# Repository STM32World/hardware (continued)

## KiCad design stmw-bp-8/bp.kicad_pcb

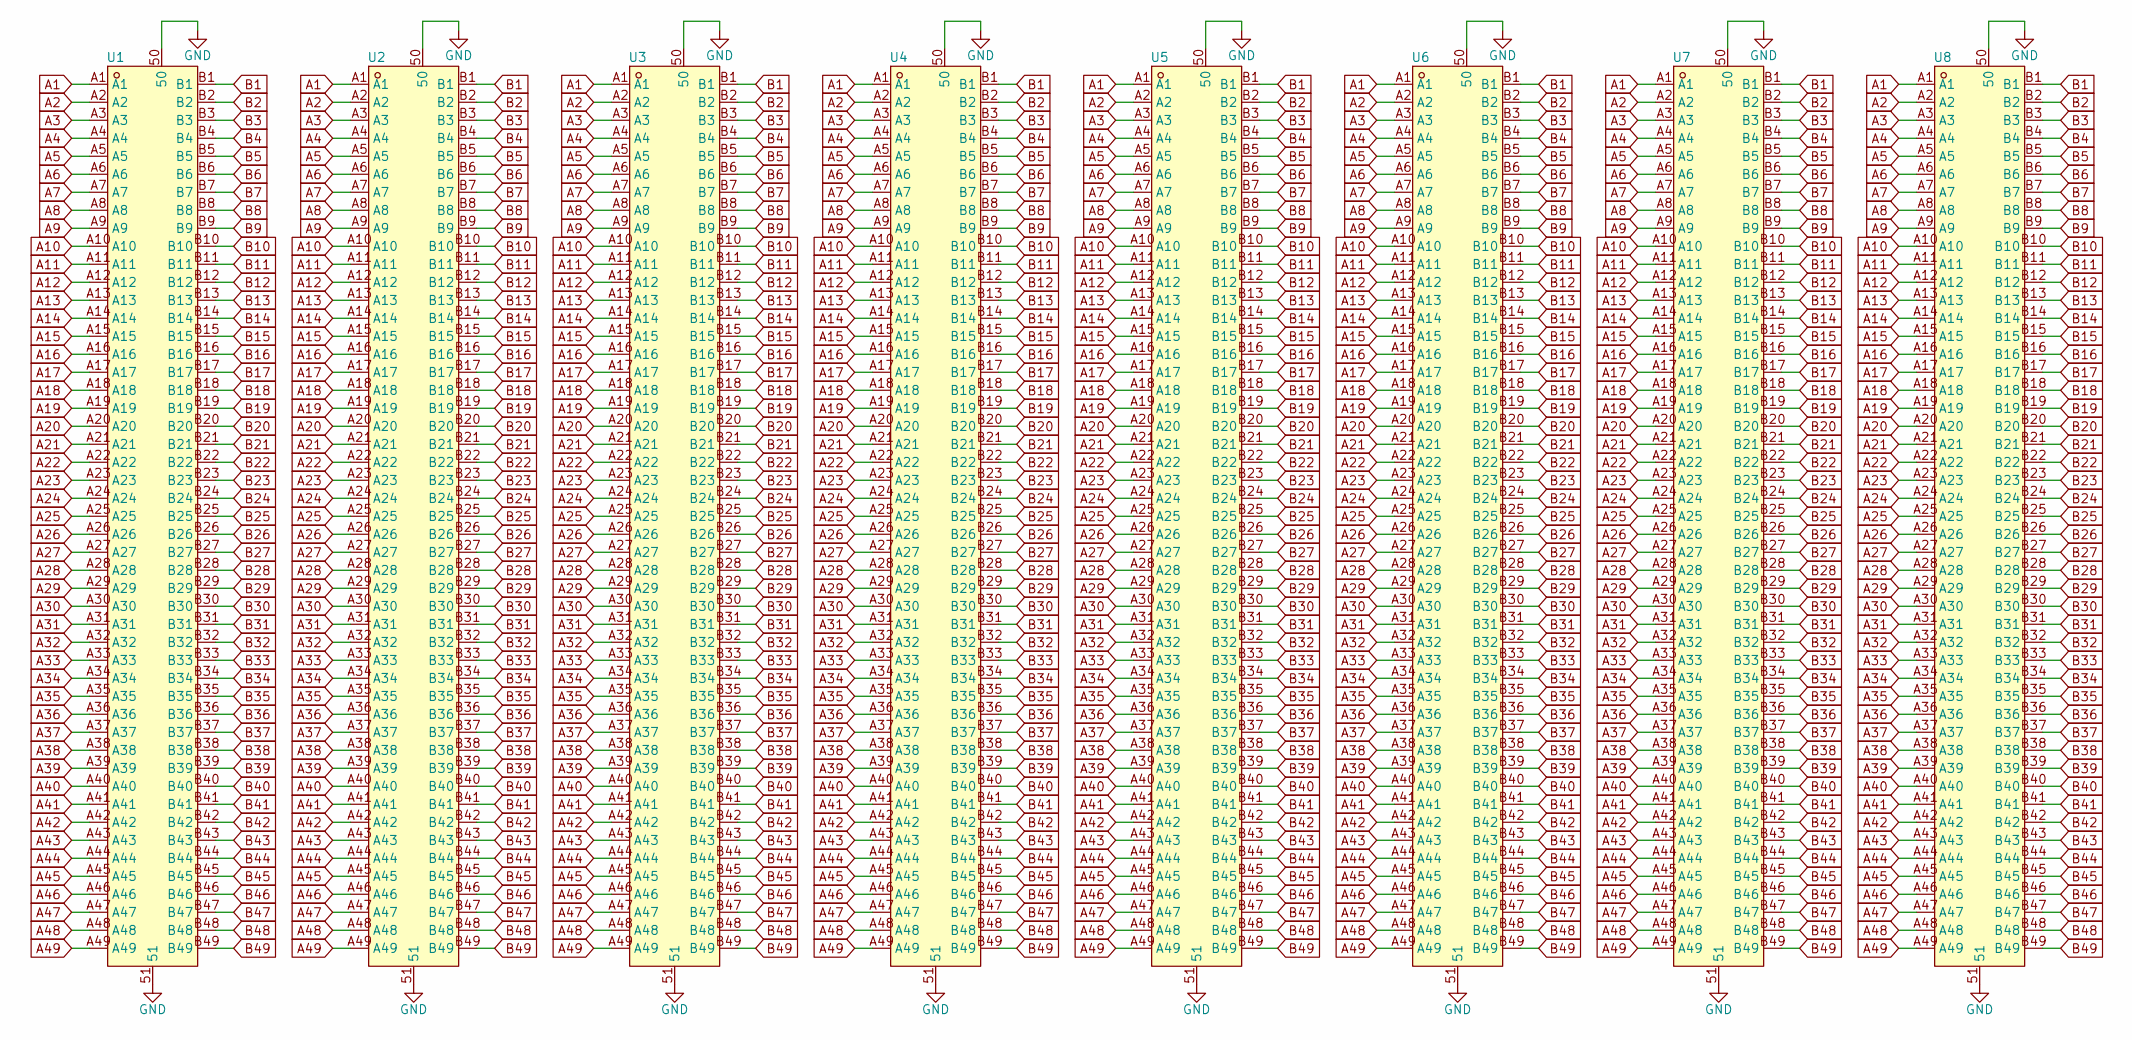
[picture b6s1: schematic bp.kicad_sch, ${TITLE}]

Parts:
U1, U2, U3, U4, U5, U6, U7, U8: X1611WVS-98-9TV01; CONN-SMD_98P-P1.00-V_3133; LCSC C21263085

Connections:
A1: U1.A1, U2.A1, U3.A1, U4.A1, U5.A1, U6.A1, U7.A1, U8.A1
A2: U1.A2, U2.A2, U3.A2, U4.A2, U5.A2, U6.A2, U7.A2, U8.A2
A3: U1.A3, U2.A3, U3.A3, U4.A3, U5.A3, U6.A3, U7.A3, U8.A3
A4: U1.A4, U2.A4, U3.A4, U4.A4, U5.A4, U6.A4, U7.A4, U8.A4
A5: U1.A5, U2.A5, U3.A5, U4.A5, U5.A5, U6.A5, U7.A5, U8.A5
A6: U1.A6, U2.A6, U3.A6, U4.A6, U5.A6, U6.A6, U7.A6, U8.A6
A7: U1.A7, U2.A7, U3.A7, U4.A7, U5.A7, U6.A7, U7.A7, U8.A7
A8: U1.A8, U2.A8, U3.A8, U4.A8, U5.A8, U6.A8, U7.A8, U8.A8
A9: U1.A9, U2.A9, U3.A9, U4.A9, U5.A9, U6.A9, U7.A9, U8.A9
A10: U1.A10, U2.A10, U3.A10, U4.A10, U5.A10, U6.A10, U7.A10, U8.A10
A11: U1.A11, U2.A11, U3.A11, U4.A11, U5.A11, U6.A11, U7.A11, U8.A11
A12: U1.A12, U2.A12, U3.A12, U4.A12, U5.A12, U6.A12, U7.A12, U8.A12
A13: U1.A13, U2.A13, U3.A13, U4.A13, U5.A13, U6.A13, U7.A13, U8.A13
A14: U1.A14, U2.A14, U3.A14, U4.A14, U5.A14, U6.A14, U7.A14, U8.A14
A15: U1.A15, U2.A15, U3.A15, U4.A15, U5.A15, U6.A15, U7.A15, U8.A15
A16: U1.A16, U2.A16, U3.A16, U4.A16, U5.A16, U6.A16, U7.A16, U8.A16
A17: U1.A17, U2.A17, U3.A17, U4.A17, U5.A17, U6.A17, U7.A17, U8.A17
A18: U1.A18, U2.A18, U3.A18, U4.A18, U5.A18, U6.A18, U7.A18, U8.A18
A19: U1.A19, U2.A19, U3.A19, U4.A19, U5.A19, U6.A19, U7.A19, U8.A19
A20: U1.A20, U2.A20, U3.A20, U4.A20, U5.A20, U6.A20, U7.A20, U8.A20
A21: U1.A21, U2.A21, U3.A21, U4.A21, U5.A21, U6.A21, U7.A21, U8.A21
A22: U1.A22, U2.A22, U3.A22, U4.A22, U5.A22, U6.A22, U7.A22, U8.A22
A23: U1.A23, U2.A23, U3.A23, U4.A23, U5.A23, U6.A23, U7.A23, U8.A23
A24: U1.A24, U2.A24, U3.A24, U4.A24, U5.A24, U6.A24, U7.A24, U8.A24
A25: U1.A25, U2.A25, U3.A25, U4.A25, U5.A25, U6.A25, U7.A25, U8.A25
A26: U1.A26, U2.A26, U3.A26, U4.A26, U5.A26, U6.A26, U7.A26, U8.A26
A27: U1.A27, U2.A27, U3.A27, U4.A27, U5.A27, U6.A27, U7.A27, U8.A27
A28: U1.A28, U2.A28, U3.A28, U4.A28, U5.A28, U6.A28, U7.A28, U8.A28
A29: U1.A29, U2.A29, U3.A29, U4.A29, U5.A29, U6.A29, U7.A29, U8.A29
A30: U1.A30, U2.A30, U3.A30, U4.A30, U5.A30, U6.A30, U7.A30, U8.A30
A31: U1.A31, U2.A31, U3.A31, U4.A31, U5.A31, U6.A31, U7.A31, U8.A31
A32: U1.A32, U2.A32, U3.A32, U4.A32, U5.A32, U6.A32, U7.A32, U8.A32
A33: U1.A33, U2.A33, U3.A33, U4.A33, U5.A33, U6.A33, U7.A33, U8.A33
A34: U1.A34, U2.A34, U3.A34, U4.A34, U5.A34, U6.A34, U7.A34, U8.A34
A35: U1.A35, U2.A35, U3.A35, U4.A35, U5.A35, U6.A35, U7.A35, U8.A35
A36: U1.A36, U2.A36, U3.A36, U4.A36, U5.A36, U6.A36, U7.A36, U8.A36
A37: U1.A37, U2.A37, U3.A37, U4.A37, U5.A37, U6.A37, U7.A37, U8.A37
A38: U1.A38, U2.A38, U3.A38, U4.A38, U5.A38, U6.A38, U7.A38, U8.A38
A39: U1.A39, U2.A39, U3.A39, U4.A39, U5.A39, U6.A39, U7.A39, U8.A39
A40: U1.A40, U2.A40, U3.A40, U4.A40, U5.A40, U6.A40, U7.A40, U8.A40
A41: U1.A41, U2.A41, U3.A41, U4.A41, U5.A41, U6.A41, U7.A41, U8.A41
A42: U1.A42, U2.A42, U3.A42, U4.A42, U5.A42, U6.A42, U7.A42, U8.A42
A43: U1.A43, U2.A43, U3.A43, U4.A43, U5.A43, U6.A43, U7.A43, U8.A43
A44: U1.A44, U2.A44, U3.A44, U4.A44, U5.A44, U6.A44, U7.A44, U8.A44
A45: U1.A45, U2.A45, U3.A45, U4.A45, U5.A45, U6.A45, U7.A45, U8.A45
A46: U1.A46, U2.A46, U3.A46, U4.A46, U5.A46, U6.A46, U7.A46, U8.A46
A47: U1.A47, U2.A47, U3.A47, U4.A47, U5.A47, U6.A47, U7.A47, U8.A47
A48: U1.A48, U2.A48, U3.A48, U4.A48, U5.A48, U6.A48, U7.A48, U8.A48
A49: U1.A49, U2.A49, U3.A49, U4.A49, U5.A49, U6.A49, U7.A49, U8.A49
B1: U1.B1, U2.B1, U3.B1, U4.B1, U5.B1, U6.B1, U7.B1, U8.B1
B2: U1.B2, U2.B2, U3.B2, U4.B2, U5.B2, U6.B2, U7.B2, U8.B2
B3: U1.B3, U2.B3, U3.B3, U4.B3, U5.B3, U6.B3, U7.B3, U8.B3
B4: U1.B4, U2.B4, U3.B4, U4.B4, U5.B4, U6.B4, U7.B4, U8.B4
B5: U1.B5, U2.B5, U3.B5, U4.B5, U5.B5, U6.B5, U7.B5, U8.B5
B6: U1.B6, U2.B6, U3.B6, U4.B6, U5.B6, U6.B6, U7.B6, U8.B6
B7: U1.B7, U2.B7, U3.B7, U4.B7, U5.B7, U6.B7, U7.B7, U8.B7
B8: U1.B8, U2.B8, U3.B8, U4.B8, U5.B8, U6.B8, U7.B8, U8.B8
B9: U1.B9, U2.B9, U3.B9, U4.B9, U5.B9, U6.B9, U7.B9, U8.B9
B10: U1.B10, U2.B10, U3.B10, U4.B10, U5.B10, U6.B10, U7.B10, U8.B10
B11: U1.B11, U2.B11, U3.B11, U4.B11, U5.B11, U6.B11, U7.B11, U8.B11
B12: U1.B12, U2.B12, U3.B12, U4.B12, U5.B12, U6.B12, U7.B12, U8.B12
B13: U1.B13, U2.B13, U3.B13, U4.B13, U5.B13, U6.B13, U7.B13, U8.B13
B14: U1.B14, U2.B14, U3.B14, U4.B14, U5.B14, U6.B14, U7.B14, U8.B14
B15: U1.B15, U2.B15, U3.B15, U4.B15, U5.B15, U6.B15, U7.B15, U8.B15
B16: U1.B16, U2.B16, U3.B16, U4.B16, U5.B16, U6.B16, U7.B16, U8.B16
B17: U1.B17, U2.B17, U3.B17, U4.B17, U5.B17, U6.B17, U7.B17, U8.B17
B18: U1.B18, U2.B18, U3.B18, U4.B18, U5.B18, U6.B18, U7.B18, U8.B18
B19: U1.B19, U2.B19, U3.B19, U4.B19, U5.B19, U6.B19, U7.B19, U8.B19
B20: U1.B20, U2.B20, U3.B20, U4.B20, U5.B20, U6.B20, U7.B20, U8.B20
B21: U1.B21, U2.B21, U3.B21, U4.B21, U5.B21, U6.B21, U7.B21, U8.B21
B22: U1.B22, U2.B22, U3.B22, U4.B22, U5.B22, U6.B22, U7.B22, U8.B22
B23: U1.B23, U2.B23, U3.B23, U4.B23, U5.B23, U6.B23, U7.B23, U8.B23
B24: U1.B24, U2.B24, U3.B24, U4.B24, U5.B24, U6.B24, U7.B24, U8.B24
B25: U1.B25, U2.B25, U3.B25, U4.B25, U5.B25, U6.B25, U7.B25, U8.B25
B26: U1.B26, U2.B26, U3.B26, U4.B26, U5.B26, U6.B26, U7.B26, U8.B26
B27: U1.B27, U2.B27, U3.B27, U4.B27, U5.B27, U6.B27, U7.B27, U8.B27
B28: U1.B28, U2.B28, U3.B28, U4.B28, U5.B28, U6.B28, U7.B28, U8.B28
B29: U1.B29, U2.B29, U3.B29, U4.B29, U5.B29, U6.B29, U7.B29, U8.B29
B30: U1.B30, U2.B30, U3.B30, U4.B30, U5.B30, U6.B30, U7.B30, U8.B30
B31: U1.B31, U2.B31, U3.B31, U4.B31, U5.B31, U6.B31, U7.B31, U8.B31
B32: U1.B32, U2.B32, U3.B32, U4.B32, U5.B32, U6.B32, U7.B32, U8.B32
B33: U1.B33, U2.B33, U3.B33, U4.B33, U5.B33, U6.B33, U7.B33, U8.B33
B34: U1.B34, U2.B34, U3.B34, U4.B34, U5.B34, U6.B34, U7.B34, U8.B34
B35: U1.B35, U2.B35, U3.B35, U4.B35, U5.B35, U6.B35, U7.B35, U8.B35
B36: U1.B36, U2.B36, U3.B36, U4.B36, U5.B36, U6.B36, U7.B36, U8.B36
B37: U1.B37, U2.B37, U3.B37, U4.B37, U5.B37, U6.B37, U7.B37, U8.B37
B38: U1.B38, U2.B38, U3.B38, U4.B38, U5.B38, U6.B38, U7.B38, U8.B38
B39: U1.B39, U2.B39, U3.B39, U4.B39, U5.B39, U6.B39, U7.B39, U8.B39
B40: U1.B40, U2.B40, U3.B40, U4.B40, U5.B40, U6.B40, U7.B40, U8.B40
B41: U1.B41, U2.B41, U3.B41, U4.B41, U5.B41, U6.B41, U7.B41, U8.B41
B42: U1.B42, U2.B42, U3.B42, U4.B42, U5.B42, U6.B42, U7.B42, U8.B42
B43: U1.B43, U2.B43, U3.B43, U4.B43, U5.B43, U6.B43, U7.B43, U8.B43
B44: U1.B44, U2.B44, U3.B44, U4.B44, U5.B44, U6.B44, U7.B44, U8.B44
B45: U1.B45, U2.B45, U3.B45, U4.B45, U5.B45, U6.B45, U7.B45, U8.B45
B46: U1.B46, U2.B46, U3.B46, U4.B46, U5.B46, U6.B46, U7.B46, U8.B46
B47: U1.B47, U2.B47, U3.B47, U4.B47, U5.B47, U6.B47, U7.B47, U8.B47
B48: U1.B48, U2.B48, U3.B48, U4.B48, U5.B48, U6.B48, U7.B48, U8.B48
B49: U1.B49, U2.B49, U3.B49, U4.B49, U5.B49, U6.B49, U7.B49, U8.B49
GND: U1.50, U1.51, U2.50, U2.51, U3.50, U3.51, U4.50, U4.51, U5.50, U5.51, U6.50, U6.51, U7.50, U7.51, U8.50, U8.51

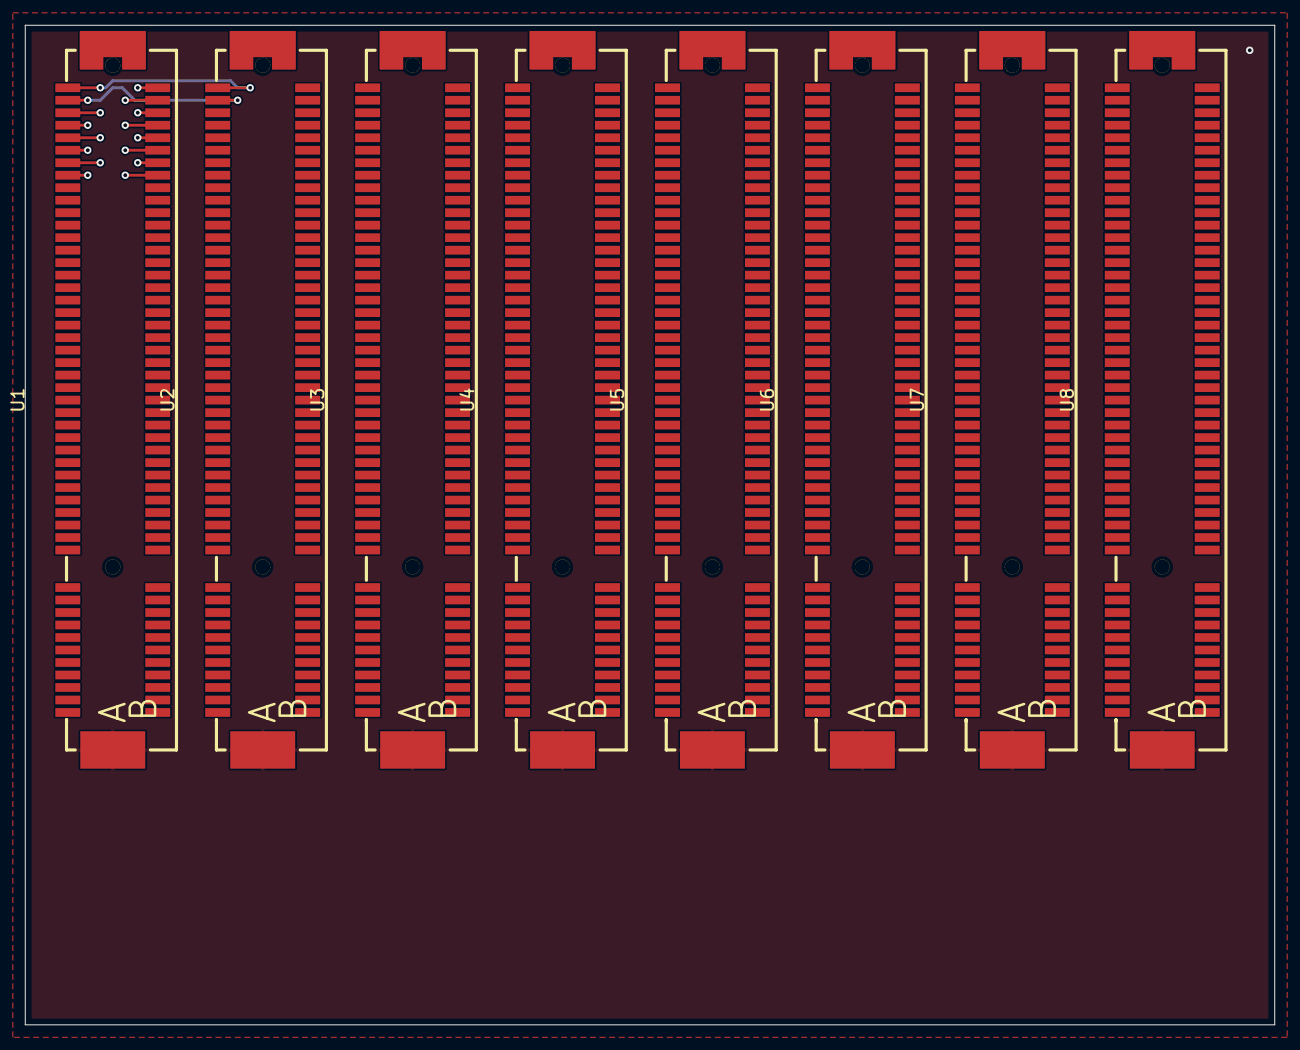
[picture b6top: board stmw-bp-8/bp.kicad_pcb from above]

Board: 2 copper layers, 100.0 x 80.0 mm, 8 parts (0 on the bottom side), 99 nets.

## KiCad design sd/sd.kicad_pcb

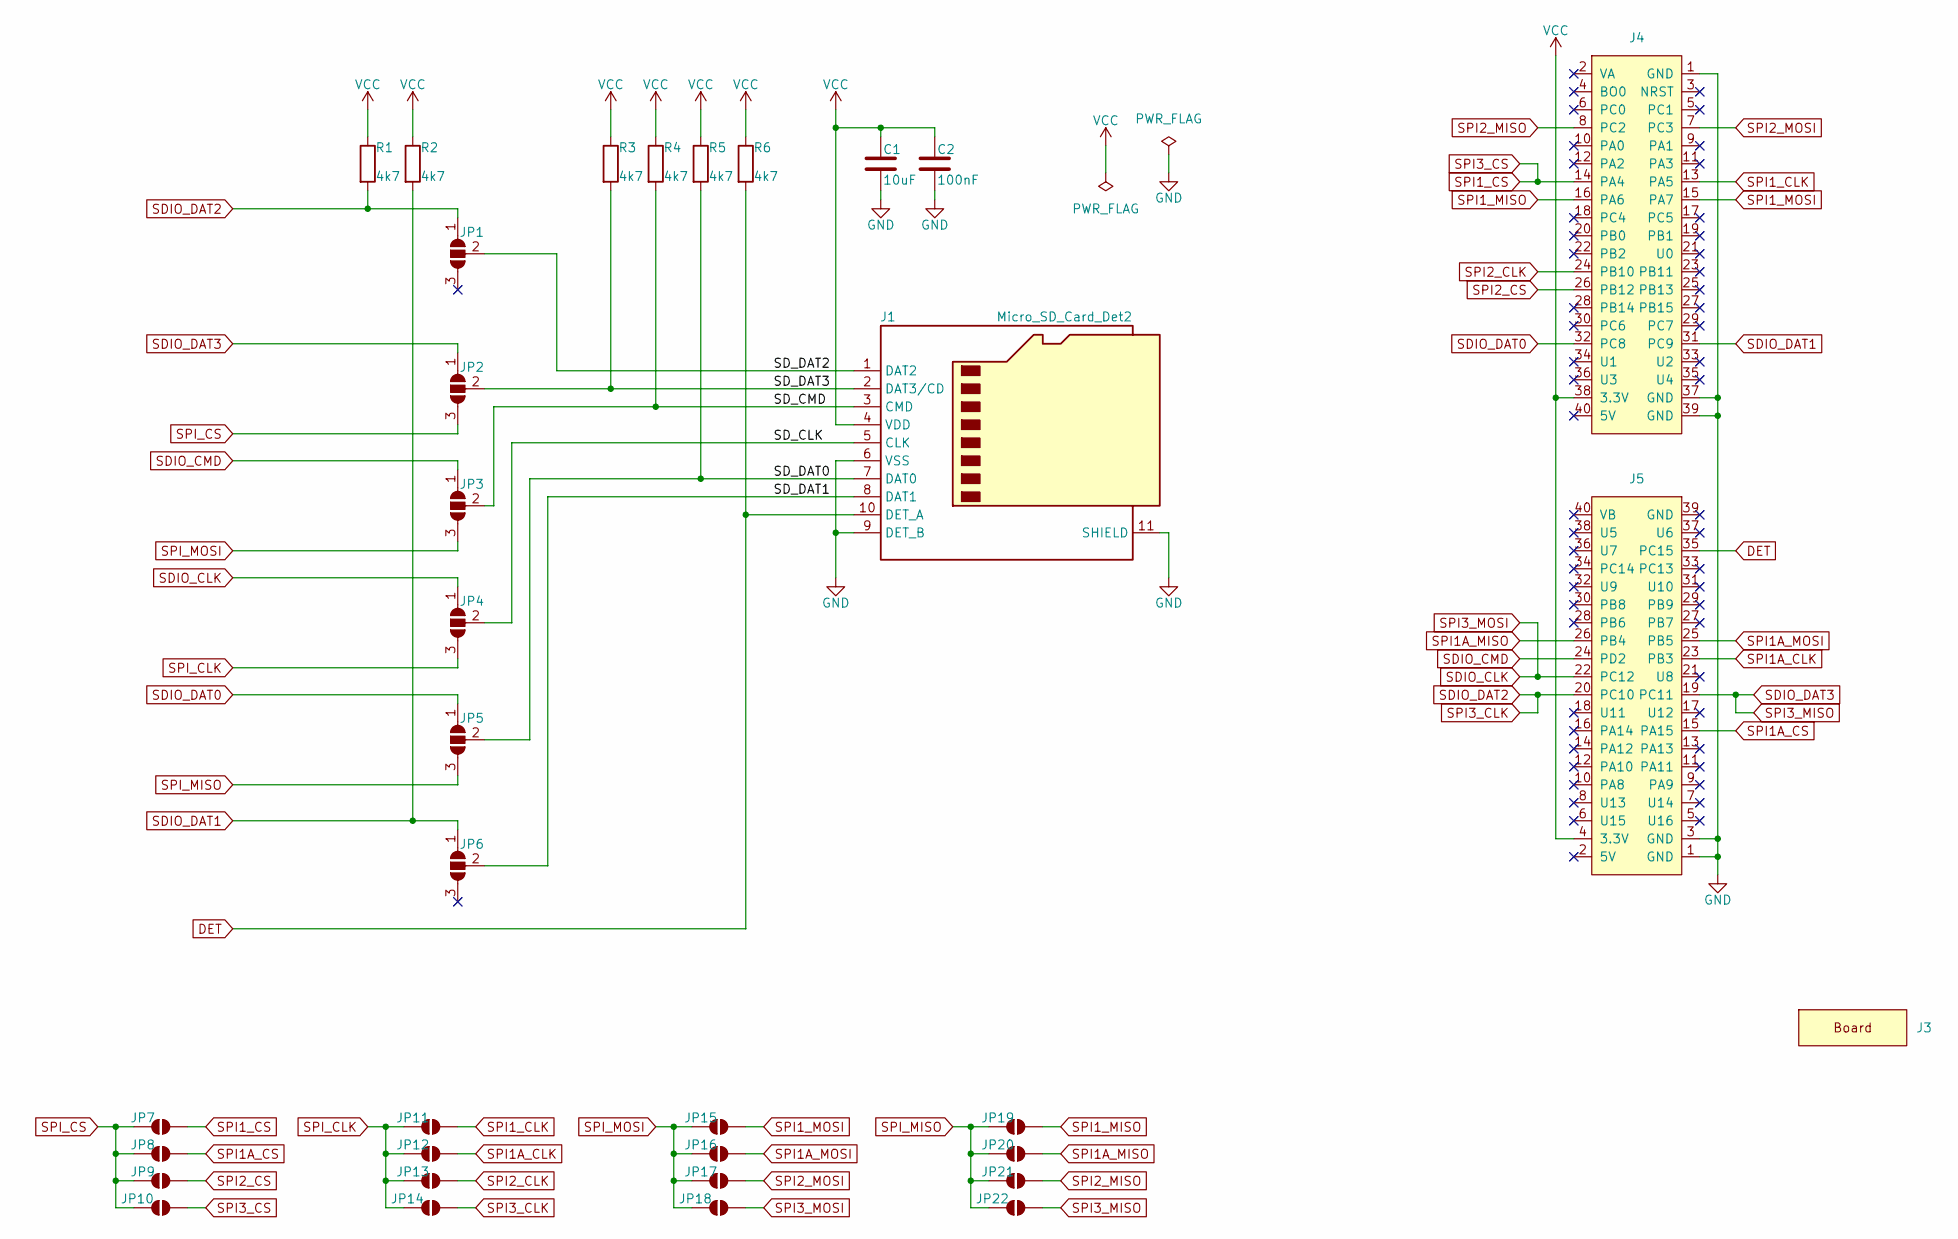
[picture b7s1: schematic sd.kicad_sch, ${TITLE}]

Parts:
C1: 10uF; C_0603_1608Metric; LCSC C1588
C2: 100nF; C_0603_1608Metric; LCSC C14663
J1: Micro_SD_Card_Det2; microSD_HC_Hirose_DM3D-SF; LCSC C719027
J3: STM32WORLD_BOARD
J4: STM32WORLD_CONNECTOR_1; PinSocket_2x20_P2.54mm_Vertical_Stackable; LCSC C35165
J5: STM32WORLD_CONNECTOR_2; PinSocket_2x20_P2.54mm_Vertical_Stackable; LCSC C35165
JP1, JP2, JP3, JP4, JP5, JP6: SolderJumper_3_Open; SolderJumper-3_P2.0mm_Open_TrianglePad1.0x1.5mm
JP7, JP8, JP9, JP10, JP11, JP12, JP13, JP14, JP15, JP16, JP17, JP18, JP19, JP20, JP21, JP22: SolderJumper_2_Open; SolderJumper-2_P1.3mm_Open_TrianglePad1.0x1.5mm
R1, R2, R3, R4, R5, R6: 4k7; R_0603_1608Metric; LCSC C23162

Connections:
/SD_CLK: J1.5 (CLK), JP4.2 (C)
/SD_CMD: J1.3 (CMD), JP3.2 (C), R4.2
/SD_DAT0: J1.7 (DAT0), JP5.2 (C), R5.2
/SD_DAT1: J1.8 (DAT1), JP6.2 (C)
/SD_DAT2: J1.1 (DAT2), JP1.2 (C)
/SD_DAT3: J1.2 (DAT3/CD), JP2.2 (C), R3.2
DET: J1.10 (DET_A), J5.35 (PC15), R6.2
GND: C1.2, C2.2, J1.6 (VSS), J1.9 (DET_B), J1.11 (SHIELD), J4.1 (GND), J4.37 (GND), J4.39 (GND), J5.1 (GND), J5.3 (GND)
SDIO_CLK: J5.22 (PC12), JP4.1 (A), JP18.2 (B)
SDIO_CMD: J5.24 (PD2), JP3.1 (A)
SDIO_DAT0: J4.32 (PC8), JP5.1 (A)
SDIO_DAT1: J4.31 (PC9), JP6.1 (A), R2.2
SDIO_DAT2: J5.20 (PC10), JP1.1 (A), JP14.2 (B), R1.2
SDIO_DAT3: J5.19 (PC11), JP2.1 (A), JP22.2 (B)
SPI1A_CLK: J5.23 (PB3), JP12.2 (B)
SPI1A_CS: J5.15 (PA15), JP8.2 (B)
SPI1A_MISO: J5.26 (PB4), JP20.2 (B)
SPI1A_MOSI: J5.25 (PB5), JP16.2 (B)
SPI1_CLK: J4.13 (PA5), JP11.2 (B)
SPI1_CS: J4.14 (PA4), JP7.2 (B), JP10.2 (B)
SPI1_MISO: J4.16 (PA6), JP19.2 (B)
SPI1_MOSI: J4.15 (PA7), JP15.2 (B)
SPI2_CLK: J4.24 (PB10), JP13.2 (B)
SPI2_CS: J4.26 (PB12), JP9.2 (B)
SPI2_MISO: J4.8 (PC2), JP21.2 (B)
SPI2_MOSI: J4.7 (PC3), JP17.2 (B)
SPI_CLK: JP4.3 (B), JP11.1 (A), JP12.1 (A), JP13.1 (A), JP14.1 (A)
SPI_CS: JP2.3 (B), JP7.1 (A), JP8.1 (A), JP9.1 (A), JP10.1 (A)
SPI_MISO: JP5.3 (B), JP19.1 (A), JP20.1 (A), JP21.1 (A), JP22.1 (A)
SPI_MOSI: JP3.3 (B), JP15.1 (A), JP16.1 (A), JP17.1 (A), JP18.1 (A)
VCC: C1.1, C2.1, J1.4 (VDD), J4.38 (3.3V), J5.4 (3.3V), R1.1, R2.1, R3.1, R4.1, R5.1, R6.1

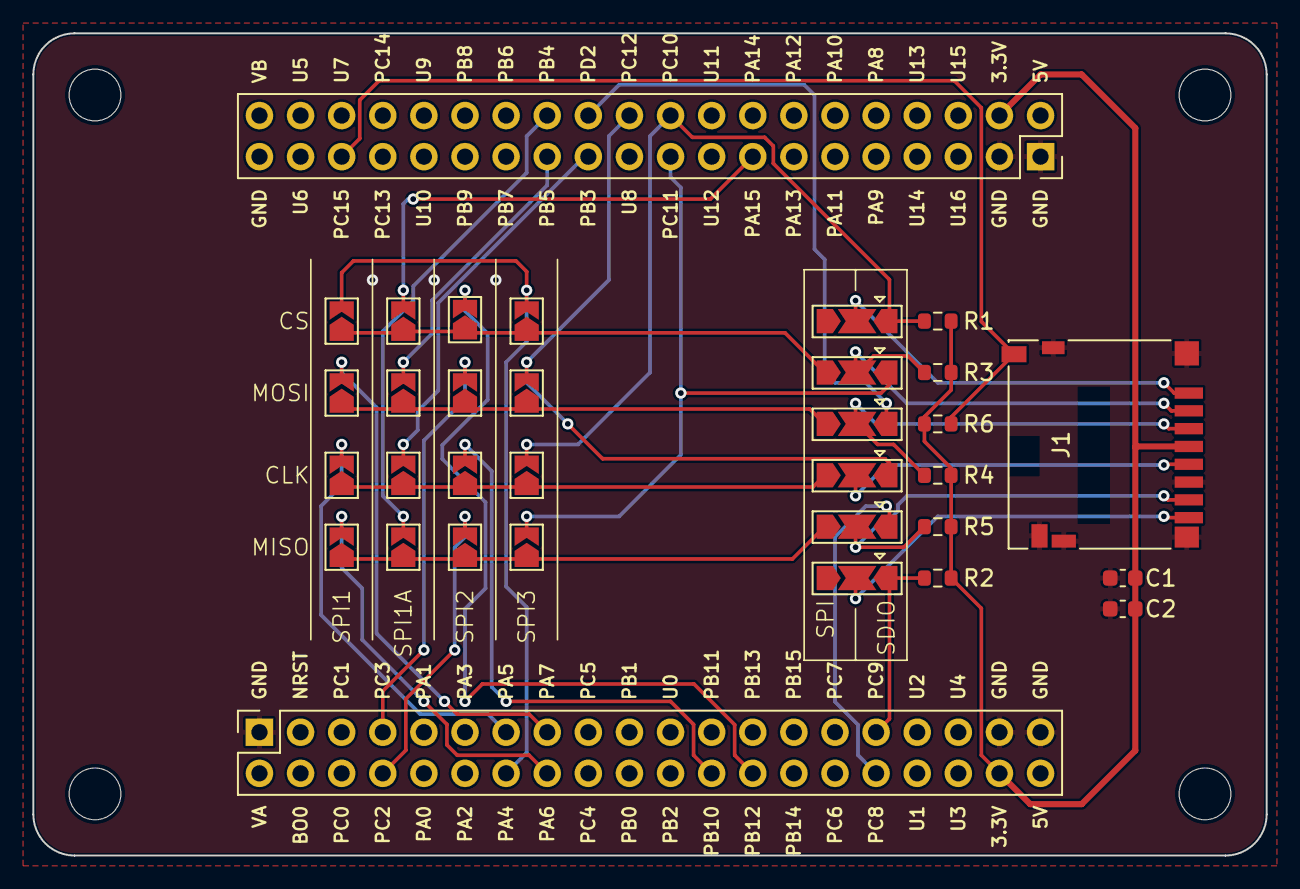
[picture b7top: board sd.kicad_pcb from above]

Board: 2 copper layers, 76.2 x 50.8 mm, 34 parts (0 on the bottom side), 31 nets.

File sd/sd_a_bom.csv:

"Reference","Qty","Value","Footprint","LCSC"
"C1","1","10uF","Capacitor_SMD:C_0603_1608Metric","C1588"
"C2","1","100nF","Capacitor_SMD:C_0603_1608Metric","C14663"
"J1","1","Micro_SD_Card_Det2","Connector_Card:microSD_HC_Hirose_DM3D-SF","C719027"
"J3","1","STM32WORLD_BOARD","stm32world:STM32WORLD_BOARD",""
"J4","1","STM32WORLD_CONNECTOR_1","stm32world:PinSocket_2x20_P2.54mm_Vertical_Stackable","C35165"
"J5","1","STM32WORLD_CONNECTOR_2","stm32world:PinSocket_2x20_P2.54mm_Vertical_Stackable","C35165"
"JP1,JP2,JP3,JP4,JP5,JP6","6","SolderJumper_3_Open","Jumper:SolderJumper-3_P2.0mm_Open_TrianglePad1.0x1.5mm",""
"JP7,JP8,JP9,JP10,JP11,JP12,JP13,JP14,JP15,JP16,JP17,JP18,JP19,JP20,JP21,JP22","16","SolderJumper_2_Open","Jumper:SolderJumper-2_P1.3mm_Open_TrianglePad1.0x1.5mm",""
"R1,R2,R3,R4,R5,R6","6","4k7","Resistor_SMD:R_0603_1608Metric","C23162"

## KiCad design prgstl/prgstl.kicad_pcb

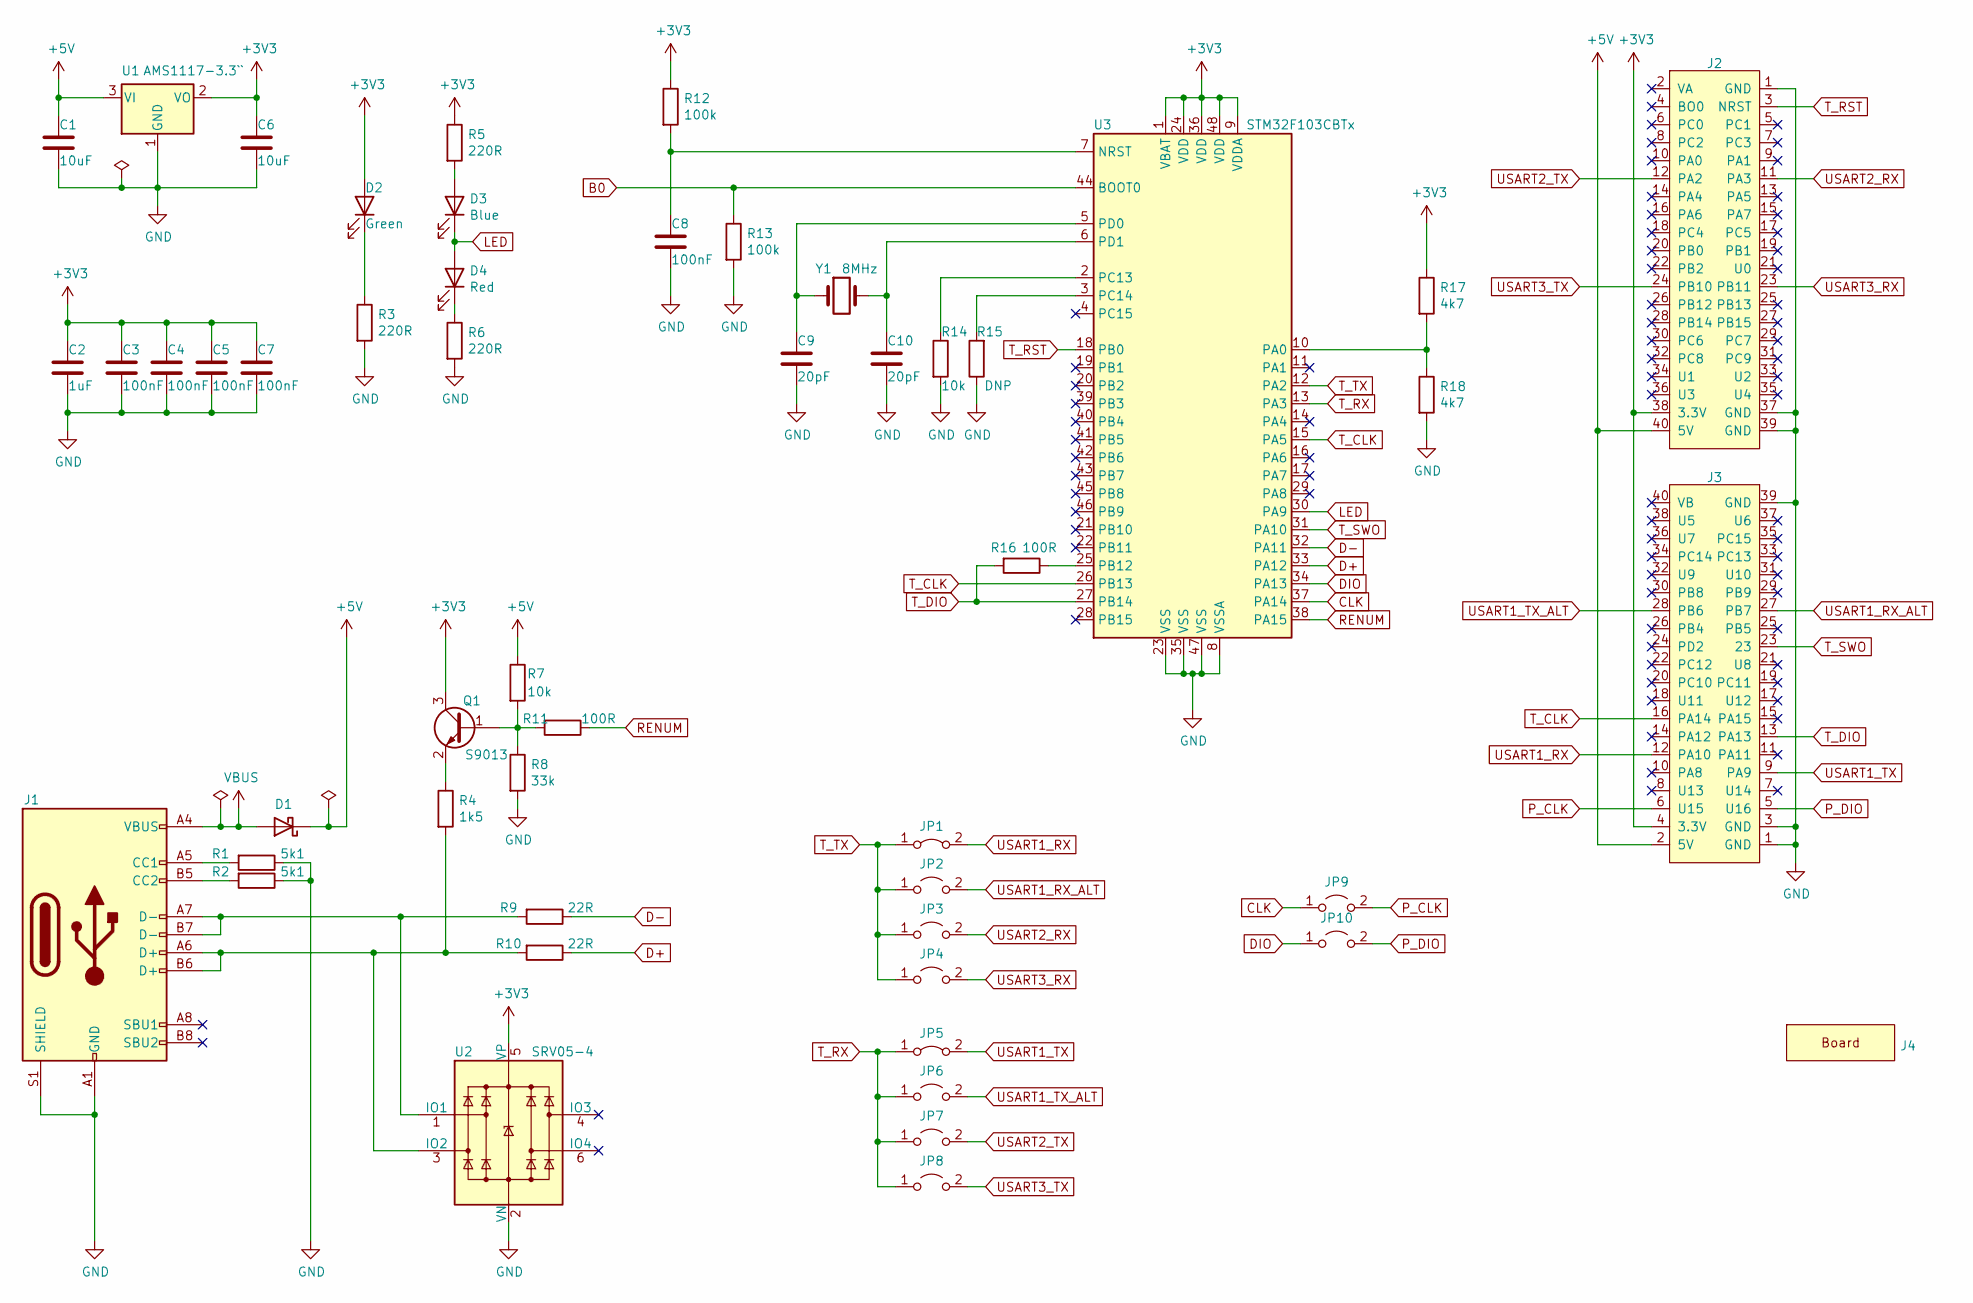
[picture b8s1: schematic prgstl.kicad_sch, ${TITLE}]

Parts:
C1, C6: C_10UF_0805; C_0805_2012Metric; LCSC C15850
C2: C_1UF_0603; C_0603_1608Metric; LCSC C15849
C3, C4, C5, C7, C8: C_100NF_0603; C_0603_1608Metric; LCSC C14663
C9, C10: C_20PF_0603; C_0603_1608Metric; LCSC C1648
D1: D_SOD-123; LCSC C8598
D2: LED_GREEN_0603; LED_0603_1608Metric; LCSC C72043
D3: LED_BLUE_0603; LED_0603_1608Metric; LCSC C72041
D4: LED_RED_0603; LED_0603_1608Metric; LCSC C2286
J1: USB_C_Receptacle_HRO_TYPE-C-31-M-12; LCSC C165948
J2: STM32WORLD_CONNECTOR_1; PinSocket_2x20_P2.54mm_Vertical_Stackable; LCSC C35165
J3: STM32WORLD_CONNECTOR_2; PinSocket_2x20_P2.54mm_Vertical_Stackable; LCSC C35165
J4: STM32WORLD_BOARD
JP1, JP5: SolderJumper-2_P1.3mm_Bridged2Bar_Pad1.0x1.5mm
JP2, JP3, JP4, JP6, JP7, JP8, JP9, JP10: SolderJumper-2_P1.3mm_Open_Pad1.0x1.5mm
Q1: S9013; SOT-23; LCSC C6749
R1, R2: R_5.1K_0603; R_0603_1608Metric; LCSC C23186
R3, R5, R6: R_220_0603; R_0603_1608Metric; LCSC C22962
R4: R_1.5K_0603; R_0603_1608Metric; LCSC C22843
R7, R14: R_10K_0603; R_0603_1608Metric; LCSC C25804
R8: R_33K_0603; R_0603_1608Metric; LCSC C4216
R9, R10: R_22_0603; R_0603_1608Metric; LCSC C23345
R11, R16: R_100_0603; R_0603_1608Metric; LCSC C22775
R12, R13: R_100K_0603; R_0603_1608Metric; LCSC C25803
R15: DNP; R_0603_1608Metric; LCSC xxC25744
R17, R18: R_4.7K_0603; R_0603_1608Metric; LCSC C23162
U1: AMS1117-3.3``; SOT-223-3_TabPin2; LCSC C6186
U2: SRV05-4; SOT-23-6; LCSC C85364
U3: STM32F103CBTx; LQFP-48_7x7mm_P0.5mm; LCSC C8304
Y1: X_8MHZ; Crystal_SMD_5032-2Pin_5.0x3.2mm; LCSC C115962

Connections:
+3V3: C2.1, C3.1, C4.1, C5.1, C6.1, C7.1, D2.2 (A), J2.38 (3.3V), J3.4 (3.3V), Q1.3 (C), R5.1, R12.1, R17.1, U1.2 (VO), U2.5 (VP), U3.1 (VBAT), U3.9 (VDDA), U3.24 (VDD), U3.36 (VDD), U3.48 (VDD)
+5V: C1.1, D1.1 (K), J2.40 (5V), J3.2 (5V), R7.1, U1.3 (VI)
B0: R13.1, U3.44 (BOOT0)
CLK: JP9.1 (A), U3.37 (PA14)
D+: R10.1, U3.33 (PA12)
D-: R9.1, U3.32 (PA11)
DIO: JP10.1 (A), U3.34 (PA13)
GND: C1.2, C2.2, C3.2, C4.2, C5.2, C6.2, C7.2, C8.2, C9.2, C10.2, J1.A1 (GND), J1.A12 (GND), J1.B1 (GND), J1.B12 (GND), J1.S1 (SHIELD), J2.1 (GND), J2.37 (GND), J2.39 (GND), J3.1 (GND), J3.3 (GND), J3.39 (GND), R1.1, R2.1, R3.2, R6.2, R8.2, R13.2, R14.2, R15.1, R18.2, U1.1 (GND), U2.2 (VN), U3.8 (VSSA), U3.23 (VSS), U3.35 (VSS), U3.47 (VSS)
LED: D3.1 (K), D4.2 (A), U3.30 (PA9)
unnamed: D2.1 (K), R3.1
unnamed: D3.2 (A), R5.2
unnamed: D4.1 (K), R6.1
unnamed: J1.A5 (CC1), R1.2
unnamed: J1.B5 (CC2), R2.2
unnamed: Q1.1 (B), R7.2, R8.1, R11.2
unnamed: Q1.2 (E), R4.1
unnamed: J1.A7 (D-), J1.B7 (D-), R9.2, U2.1 (IO1)
unnamed: J1.A6 (D+), J1.B6 (D+), R4.2, R10.2, U2.3 (IO2)
unnamed: C8.1, R12.2, U3.7 (NRST)
unnamed: R17.2, R18.1, U3.10 (PA0)
unnamed: R16.1, U3.25 (PB12)
unnamed: R14.1, U3.2 (PC13)
unnamed: R15.2, U3.3 (PC14)
unnamed: C9.1, U3.5 (PD0), Y1.1
unnamed: C10.1, U3.6 (PD1), Y1.2
P_CLK: J3.6 (U15), JP9.2 (B)
P_DIO: J3.5 (U16), JP10.2 (B)
RENUM: R11.1, U3.38 (PA15)
T_CLK: J3.16 (PA14), U3.15 (PA5), U3.26 (PB13)
T_DIO: J3.13 (PA13), R16.2, U3.27 (PB14)
T_RST: J2.3 (NRST), U3.18 (PB0)
T_RX: JP5.1 (A), JP6.1 (A), JP7.1 (A), JP8.1 (A), U3.13 (PA3)
T_SWO: J3.23, U3.31 (PA10)
T_TX: JP1.1 (A), JP2.1 (A), JP3.1 (A), JP4.1 (A), U3.12 (PA2)
USART1_RX: J3.12 (PA10), JP1.2 (B)
USART1_RX_ALT: J3.27 (PB7), JP2.2 (B)
USART1_TX: J3.9 (PA9), JP5.2 (B)
USART1_TX_ALT: J3.28 (PB6), JP6.2 (B)
USART2_RX: J2.11 (PA3), JP3.2 (B)
USART2_TX: J2.12 (PA2), JP7.2 (B)
USART3_RX: J2.23 (PB11), JP4.2 (B)
USART3_TX: J2.24 (PB10), JP8.2 (B)
VBUS: D1.2 (A), J1.A4 (VBUS), J1.A9 (VBUS), J1.B4 (VBUS), J1.B9 (VBUS)

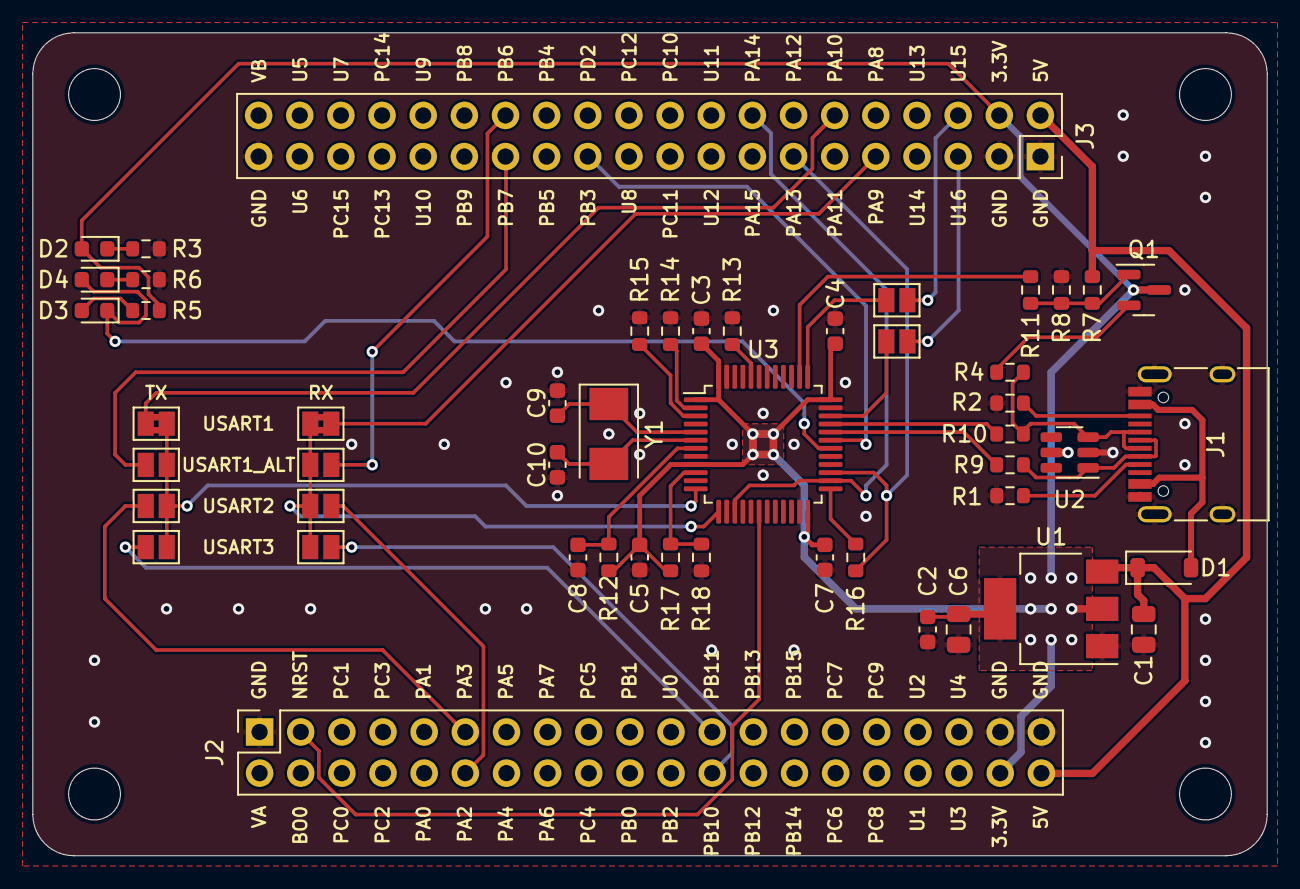
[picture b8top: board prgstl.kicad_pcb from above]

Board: 2 copper layers, 76.2 x 50.8 mm, 51 parts (0 on the bottom side), 43 nets.

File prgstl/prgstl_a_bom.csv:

Comment,Designator,Footprint,Display,LCSC
"C_10UF_0805","C1,C6","Capacitor_SMD:C_0805_2012Metric","10uF","C15850"
"C_1UF_0603","C2","Capacitor_SMD:C_0603_1608Metric","1uF","C15849"
"C_100NF_0603","C3,C4,C5,C7,C8","Capacitor_SMD:C_0603_1608Metric","100nF","C14663"
"C_20PF_0603","C9,C10","Capacitor_SMD:C_0603_1608Metric","20pF","C1648"
"~","D1","Diode_SMD:D_SOD-123","","C8598"
"LED_GREEN_0603","D2","LED_SMD:LED_0603_1608Metric","Green","C72043"
"LED_BLUE_0603","D3","LED_SMD:LED_0603_1608Metric","Blue","C72041"
"LED_RED_0603","D4","LED_SMD:LED_0603_1608Metric","Red","C2286"
"~","J1","stm32world:USB_C_Receptacle_HRO_TYPE-C-31-M-12","","C165948"
"STM32WORLD_CONNECTOR_1","J2","stm32world:PinSocket_2x20_P2.54mm_Vertical_Stackable","","C35165"
"STM32WORLD_CONNECTOR_2","J3","stm32world:PinSocket_2x20_P2.54mm_Vertical_Stackable","","C35165"
"STM32WORLD_BOARD","J4","stm32world:STM32WORLD_BOARD"
"~","JP1,JP5","Jumper:SolderJumper-2_P1.3mm_Bridged2Bar_Pad1.0x1.5mm"
"~","JP2,JP3,JP4,JP6,JP7,JP8,JP9,JP10","Jumper:SolderJumper-2_P1.3mm_Open_Pad1.0x1.5mm"
"S9013","Q1","Package_TO_SOT_SMD:SOT-23","","C6749"
"R_5.1K_0603","R1,R2","Resistor_SMD:R_0603_1608Metric","5k1","C23186"
"R_100_0603","R11,R16","Resistor_SMD:R_0603_1608Metric","100R","C22775"
"R_100K_0603","R12,R13","Resistor_SMD:R_0603_1608Metric","100k","C25803"
"DNP","R15","Resistor_SMD:R_0603_1608Metric","","xxC25744"
"R_4.7K_0603","R17,R18","Resistor_SMD:R_0603_1608Metric","4k7","C23162"
"R_220_0603","R3,R5,R6","Resistor_SMD:R_0603_1608Metric","220R","C22962"
"R_1.5K_0603","R4","Resistor_SMD:R_0603_1608Metric","1k5","C22843"
"R_10K_0603","R7,R14","Resistor_SMD:R_0603_1608Metric","10k","C25804"
"R_33K_0603","R8","Resistor_SMD:R_0603_1608Metric","33k","C4216"
"R_22_0603","R9,R10","Resistor_SMD:R_0603_1608Metric","22R","C23345"
"AMS1117-3.3``","U1","Package_TO_SOT_SMD:SOT-223-3_TabPin2","","C6186"
"SRV05-4","U2","Package_TO_SOT_SMD:SOT-23-6","","C85364"
"STM32F103CBTx","U3","Package_QFP:LQFP-48_7x7mm_P0.5mm","","C8304"
"X_8MHZ","Y1","stm32world:Crystal_SMD_5032-2Pin_5.0x3.2mm","8MHz","C115962"

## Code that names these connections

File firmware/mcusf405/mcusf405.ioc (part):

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PC3.Mode=Full_Duplex_Master
PA6.Mode=Full_Duplex_Master
PH0-OSC_IN.Signal=RCC_OSC_IN
Mcu.UserName=STM32F405RGTx
PB10.Mode=Full_Duplex_Master
PC10.Signal=SDIO_D2
PC12.Signal=SDIO_CK
PA11.Mode=OTG/Dual_Role_Device
PB13.Signal=CAN2_TX
PA12.Signal=USB_OTG_FS_DP
PB6.Signal=USART1_TX
PB6.Mode=Asynchronous
PC3.Signal=SPI2_MOSI
PH0-OSC_IN.Mode=HSE-External-Oscillator
RCC.HSE_VALUE=25000000
PB3.Mode=Trace_Asynchronous_SW
PC14-OSC32_IN.Mode=LSE-External-Oscillator
PA14.Mode=Trace_Asynchronous_SW
PC9.Mode=SD_4_bits_Wide_bus
PB7.Signal=USART1_RX
PH1-OSC_OUT.Mode=HSE-External-Oscillator
Mcu.Package=LQFP64
PB9.Signal=I2C1_SDA
PA6.Signal=SPI1_MISO
PB12.Mode=CAN_Activate
PA10.Signal=USB_OTG_FS_ID
PC11.Mode=SD_4_bits_Wide_bus
PB13.Mode=CAN_Activate
PA3.Signal=USART2_RX
PA5.Mode=Full_Duplex_Master
PC15-OSC32_OUT.Mode=LSE-External-Oscillator
PA7.Mode=Full_Duplex_Master
PA10.Mode=OTG/Dual_Role_Device
PC11.Signal=SDIO_D3
PC8.Signal=SDIO_D0
PC2.Signal=SPI2_MISO
PC10.Mode=SD_4_bits_Wide_bus
PC2.Mode=Full_Duplex_Master
PC14-OSC32_IN.Signal=RCC_OSC32_IN
PA13.Signal=SYS_JTMS-SWDIO
PA3.Mode=Asynchronous
PA9.Mode=Activate_VBUS
PB9.Mode=I2C
PA9.Signal=USB_OTG_FS_VBUS
PC15-OSC32_OUT.Signal=RCC_OSC32_OUT
PB10.Signal=SPI2_SCK
PD2.Mode=SD_4_bits_Wide_bus
PA5.Signal=SPI1_SCK
PC12.Mode=SD_4_bits_Wide_bus
board=custom
PH1-OSC_OUT.Signal=RCC_OSC_OUT
PA13.Mode=Trace_Asynchronous_SW
Mcu.Name=STM32F405RGTx
PA2.Signal=USART2_TX
PC8.Mode=SD_4_bits_Wide_bus
PB3.Signal=SYS_JTDO-SWO
RCC.SYSCLKFreq_VALUE=16000000
PA12.Mode=OTG/Dual_Role_Device
PB7.Mode=Asynchronous
PA11.Signal=USB_OTG_FS_DM
PA14.Signal=SYS_JTCK-SWCLK
PB8.Mode=I2C
PA2.Mode=Asynchronous
PB8.Signal=I2C1_SCL
PC9.Signal=SDIO_D1
PD2.Signal=SDIO_CMD
PB12.Signal=CAN2_RX
PA7.Signal=SPI1_MOSI

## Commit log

2021-06-15 Hmmmm
2021-06-15 Hmmm
2021-07-14 Reorganized
2021-07-14 Moving
2021-07-14 Renamed module to match wiki
2021-07-15 Created ioaw9523
2021-07-16 Added blank!
2021-07-16 Added SPI Flash Module MEMW25Q128
2022-05-04 Getting there
2022-05-05 Almost there
2022-09-10 Playing with ordering files
2022-09-11 Still messing with ordering files
2022-09-11 memw25q128 order files done and working
2022-09-12 memw25q128 order files confirmed
2022-09-12 mcustm32f446 orders ok
2022-09-12 Ordering process work
2022-09-14 Order files acceptable
2022-09-18 Changing connector symbol and footprints
2022-09-18 MCUSTM32F405 should be ready for order
2022-09-18 Tweaking
2022-09-27 Changed jumpers on memw25qxx
2023-07-13 Ready to order prgctl
2023-07-13 Ready to order mcustm32f405
2023-07-13 mem25q128 ready to order
2023-07-22 Jumpers for nrst and b0 on header.
2023-08-05 Playing with mcustm32mp151
2023-08-25 mem24cxx ready
2023-09-11 Wired B0 to PC15 so it can be read
2023-10-28 Tweaks
2023-12-03 fixed label
2023-12-12 Ordering can rev_a
2023-12-22 Fixed bug in cantrans
2024-02-21 Started working on led
2024-02-25 More
2024-06-11 Ordered sec01 rev a
2025-05-30 Ready for order
2025-06-13 New sd
2025-06-14 Working on sd
2025-06-14 Schematics verified- tweaking pcb
2025-06-14 Ordered sd rev a
2025-07-07 Started working on stmw2
2025-07-07 Workin on backplane
2025-07-08 Tweaking backplane
2025-07-08 Moving workstation
2025-08-16 Created stmw-bp-5
2025-09-15 DRC with no error
